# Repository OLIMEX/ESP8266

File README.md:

README
======

These apps accomplish the following:

-- ESP8266-EVB-blinkLED : Blink by green LED on ESP8266-EVB

-- arduino_style :

-- esphttpd : Advanced web-server for ESP8266-EVB (Config, Rele, Button).

## Build toolchain

https://github.com/pfalcon/esp-open-sdk is easy to use, it basically does all on its own.

- Clone the repository to ```/opt/Espressif``` (or somewhere else, this path seems to be preferred by some people)
- Install dependencies: ```sudo apt-get install make unrar-free autoconf automake libtool gcc g++ gperf flex bison texinfo gawk ncurses-dev libexpat-dev python sed help2man```
- ```make```, not as root - wait a few minutes, done.
- Add ```export PATH="${PATH}:/opt/Espressif/xtensa-lx106-elf/bin"``` to your .bashrc, .profile, .zshrc, whatever. Or just run it every time you want to use the toolchain.

In some versions of the SDK there seems to be a problem with some type definitions. If you have problems compiling with errors that some types are not defined try opening ```xtensa-lx106-elf/xtensa-lx106-elf/sysroot/usr/include/c_types.h``` and replace ```#if 0``` near the top with ```#if 1```.

## Get esptool

Some projects use ```esptool```, which is something completely different as ```esptool.py``` and which is not installed by ```esp-open-sdk```. You can get ```esptool``` here: 
* https://github.com/tommie/esptool-ck 

or here: 
* https://github.com/themadinventor/esptool

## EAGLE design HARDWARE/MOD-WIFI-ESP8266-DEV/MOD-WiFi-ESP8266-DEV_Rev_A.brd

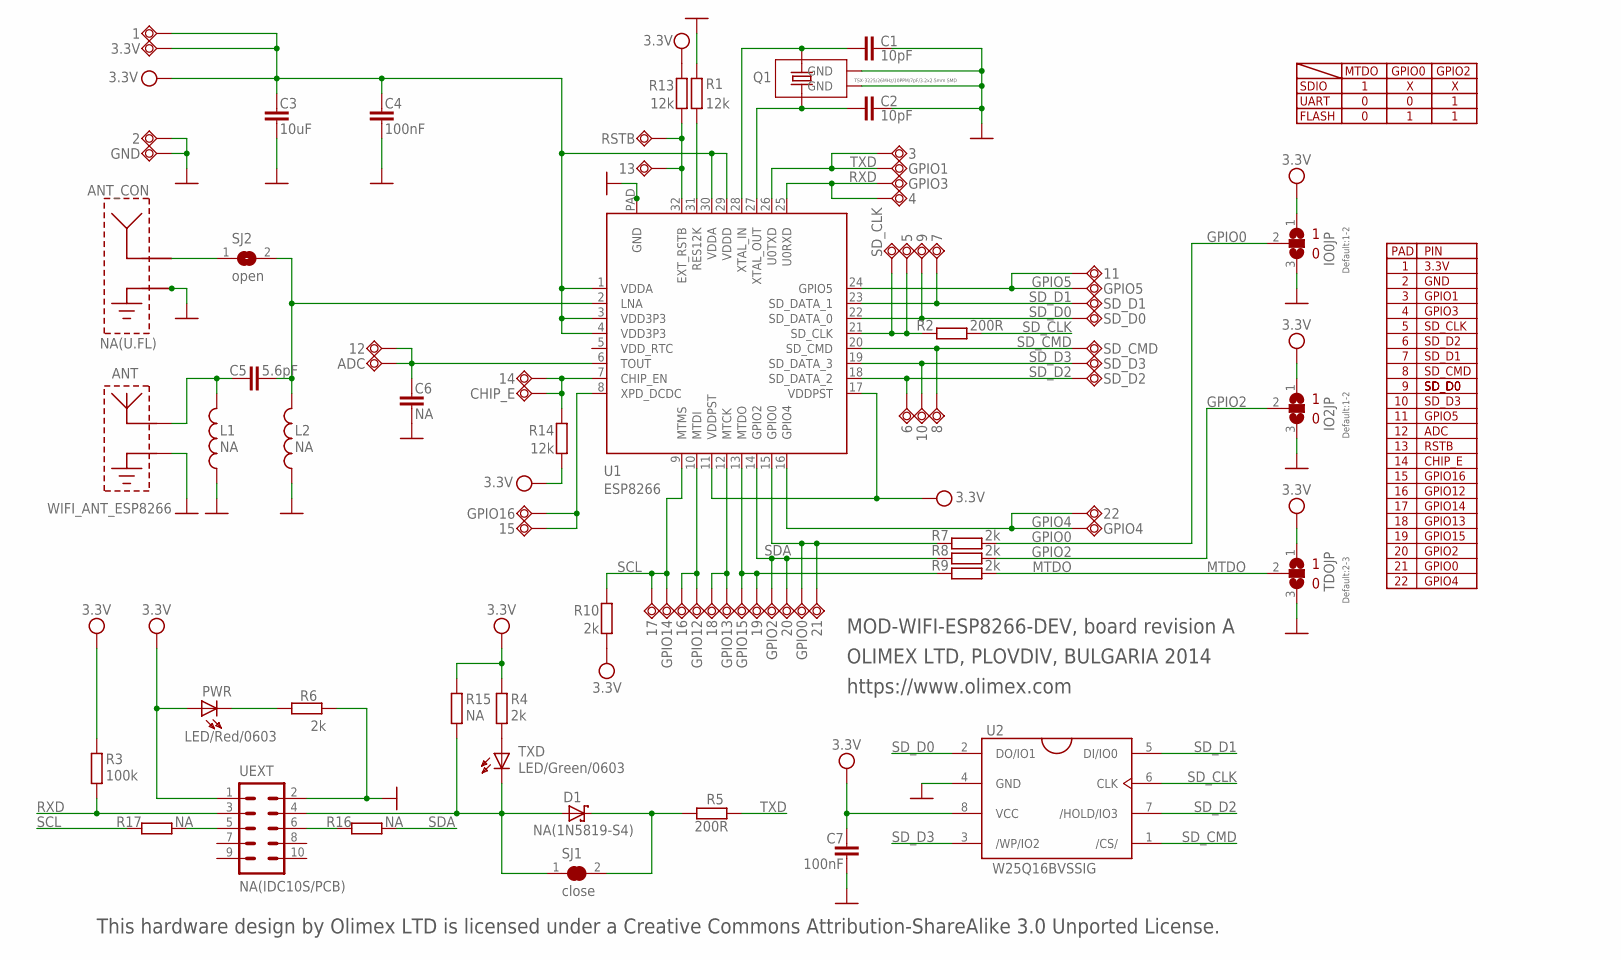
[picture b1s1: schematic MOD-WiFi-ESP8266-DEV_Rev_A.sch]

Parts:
1, 2, 3, 4, 5, 6, 7, 8, 9, 10, 11, 12, 13, 14, 15, 16, 17, 18, 19, 20, 21, 22: TESTPAD8; TESTPAD50/80
3.3V: TESTPAD40/66
ADC: TESTPAD40/66
ANT: WIFI_ANT_ESP8266; ESP8266_ANT
ANT_CON: NA(U.FL); RF_CONNECTOR_I-PEX
C1, C2: 10pF; C0402_TI
C3: 10uF; C0603_DWS
C4, C7: 100nF; C0402_TI
C5: 5.6pF; C0402_TI
C6: NA; C0402_TI
CHIP_E: TESTPAD40/66
D1: NA(1N5819-S4); SOD-123
GND: TESTPAD40/66
GPIO0, GPIO1, GPIO2, GPIO3, GPIO4, GPIO5, GPIO12, GPIO13, GPIO14, GPIO15, GPIO16: TESTPAD40/66
IO0JP, IO2JP: Default:1-2; SJ_2_SMALLER
L1, L2: NA; L0402_TI
PWR: LED/Red/0603; LED_0603
Q1: TSX-3225/26MHz/10PPM/7pF/3.2x2.5mm SMD; NX3225SA
R1, R13, R14: 12k; R0402_TI
R2, R5: 200R; R0402_TI
R3: 100k; R0402_TI
R4, R6, R7, R8, R9, R10: 2k; R0402_TI
R15, R16, R17: NA; R0402_TI
RSTB: TESTPAD40/66
SD_CLK: TESTPAD40/66
SD_CMD: TESTPAD40/66
SD_D0, SD_D1, SD_D2, SD_D3: TESTPAD40/66
SJ1: close; SJ_1_SMALLER_CLOSE_10MILS
SJ2: open; SJ_1_SMALLER
TDOJP: Default:2-3; SJ_2_SMALLER
TXD: LED/Green/0603; LED_0603
U1: ESP8266; QFN32_PAD
U2: W25Q16BVSSIG; SO8_ATMEL_FLASH
UEXT: NA(IDC10S/PCB); ML10L_PADS_FEMAIL

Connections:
GND: 2.P$1, ANT.GND, ANT_CON.1 (GND_1), ANT_CON.2 (GND_2), C1.1, C2.1, C3.2, C4.2, C6.2, C7.2, GND.P$1, IO0JP.3, IO2JP.3, L1.1, L2.1, Q1.NC_1 (GND), Q1.NC_2 (GND), R1.2, R6.1, TDOJP.3, U1.P$1 (GND), U1.P$2 (GND), U1.P$3 (GND), U1.P$4 (GND), U1.P$5 (GND), U1.P$6 (GND), U1.P$7 (GND), U1.P$8 (GND), U1.P$9 (GND), U1.PAD (GND), U2.4 (GND), UEXT.2
GPIO0: IO0JP.2, R7.1
GPIO2: IO2JP.2, R8.1
GPIO4: 22.P$1, GPIO4.P$1, U1.16 (GPIO4)
GPIO5: 11.P$1, GPIO5.P$1, U1.24 (GPIO5)
MTDO: R9.1, TDOJP.2
unnamed: D1.A, R15.1, SJ1.1, TXD.C, UEXT.4
unnamed: R4.1, TXD.A
unnamed: PWR.C, R6.2
unnamed: 21.P$1, GPIO0.P$1, R7.2, U1.15 (GPIO0)
unnamed: ANT_CON.ANT, SJ2.1
unnamed: 19.P$1, GPIO15.P$1, R9.2, U1.13 (MTDO)
unnamed: 15.P$1, GPIO16.P$1, U1.8 (XPD_DCDC)
unnamed: 16.P$1, GPIO12.P$1, U1.10 (MTDI)
unnamed: 18.P$1, GPIO13.P$1, U1.12 (MTCK)
unnamed: 14.P$1, CHIP_E.P$1, R14.1, U1.7 (CHIP_EN)
unnamed: C5.2, L2.2, SJ2.2, U1.2 (LNA)
unnamed: 13.P$1, R13.2, RSTB.P$1, U1.32 (EXT_RSTB)
unnamed: ANT.ANT, C5.1, L1.2
unnamed: D1.C, R5.2, SJ1.2
unnamed: R17.2, UEXT.5
unnamed: R16.1, UEXT.6
unnamed: 12.P$1, ADC.P$1, C6.1, U1.6 (TOUT)
unnamed: C2.2, Q1.2, U1.27 (XTAL_OUT)
unnamed: R1.1, U1.31 (RES12K)
unnamed: C1.2, Q1.1, U1.28 (XTAL_IN)
unnamed: 5.P$1, R2.2, SD_CLK.P$1, U1.21 (SD_CLK)
RXD: 4.P$1, GPIO3.P$1, R3.1, U1.25 (U0RXD), UEXT.3
SCL: 17.P$1, GPIO14.P$1, R10.1, R17.1, U1.9 (MTMS)
SDA: 20.P$1, GPIO2.P$1, R8.2, R16.2, U1.14 (GPIO2)
SD_CLK: R2.1, U2.6 (CLK)
SD_CMD: 8.P$1, SD_CMD.P$1, U1.20 (SD_CMD), U2.1 (/CS/)
SD_D0: 9.P$1, SD_D0.P$1, U1.22 (SD_DATA_0), U2.2 (DO/IO1)
SD_D1: 7.P$1, SD_D1.P$1, U1.23 (SD_DATA_1), U2.5 (DI/IO0)
SD_D2: 6.P$1, SD_D2.P$1, U1.18 (SD_DATA_2), U2.7 (/HOLD/IO3)
SD_D3: 10.P$1, SD_D3.P$1, U1.19 (SD_DATA_3), U2.3 (/WP/IO2)
TXD: 3.P$1, GPIO1.P$1, R5.1, U1.26 (U0TXD)
VCC: 1.P$1, 3.3V.P$1, C3.1, C4.1, C7.1, IO0JP.1, IO2JP.1, PWR.A, R3.2, R4.2, R10.2, R13.1, R14.2, R15.2, TDOJP.1, U1.1 (VDDA), U1.3 (VDD3P3), U1.4 (VDD3P3), U1.11 (VDDPST), U1.17 (VDDPST), U1.29 (VDDD), U1.30 (VDDA), U2.8 (VCC), UEXT.1

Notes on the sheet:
SDIO
UART
FLASH
MTDO
GPIO0
GPIO2
PAD
GPIO1
GPIO3
SD_CLK
SD_D0
SD_D1
SD_D2
SD_D3
SD_CMD
3.3V
GND
GPIO5
GPIO4
GPIO15
GPIO13
GPIO12
GPIO14
GPIO16
ADC
PIN
RSTB
CHIP_E
MOD-WIFI-ESP8266-DEV, board revision A
OLIMEX LTD, PLOVDIV, BULGARIA 2014
This hardware design by Olimex LTD is licensed under a Creative Commons Attribution-ShareAlike 3.0 Unported License.
https://www.olimex.com

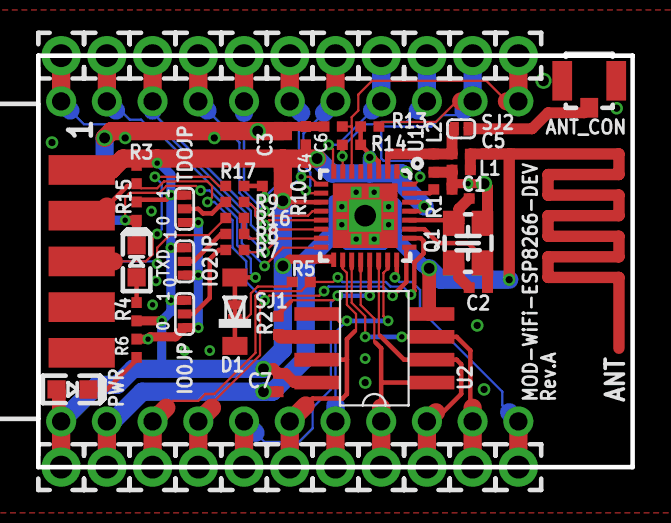
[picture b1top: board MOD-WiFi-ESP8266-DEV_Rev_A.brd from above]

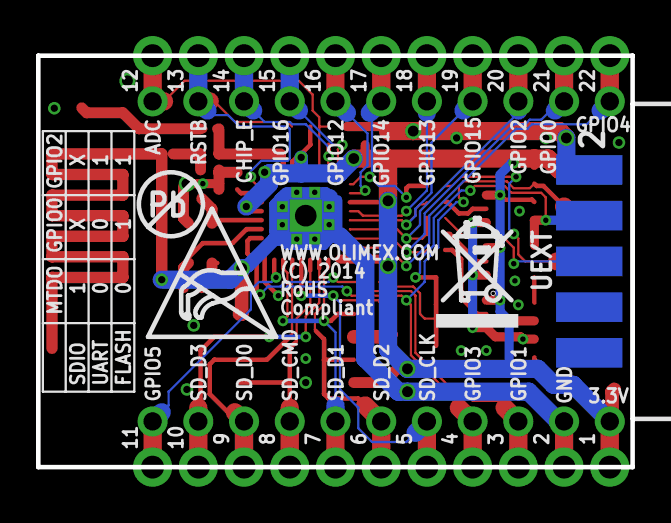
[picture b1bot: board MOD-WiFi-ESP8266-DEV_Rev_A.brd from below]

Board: 2 copper layers, 33.0 x 22.9 mm, 85 parts (4 on the bottom side), 38 nets.

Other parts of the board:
U$4: ESD_SYMBOL
U$6: PB_SMALL
U$7: RECYCLE_BIN1/8

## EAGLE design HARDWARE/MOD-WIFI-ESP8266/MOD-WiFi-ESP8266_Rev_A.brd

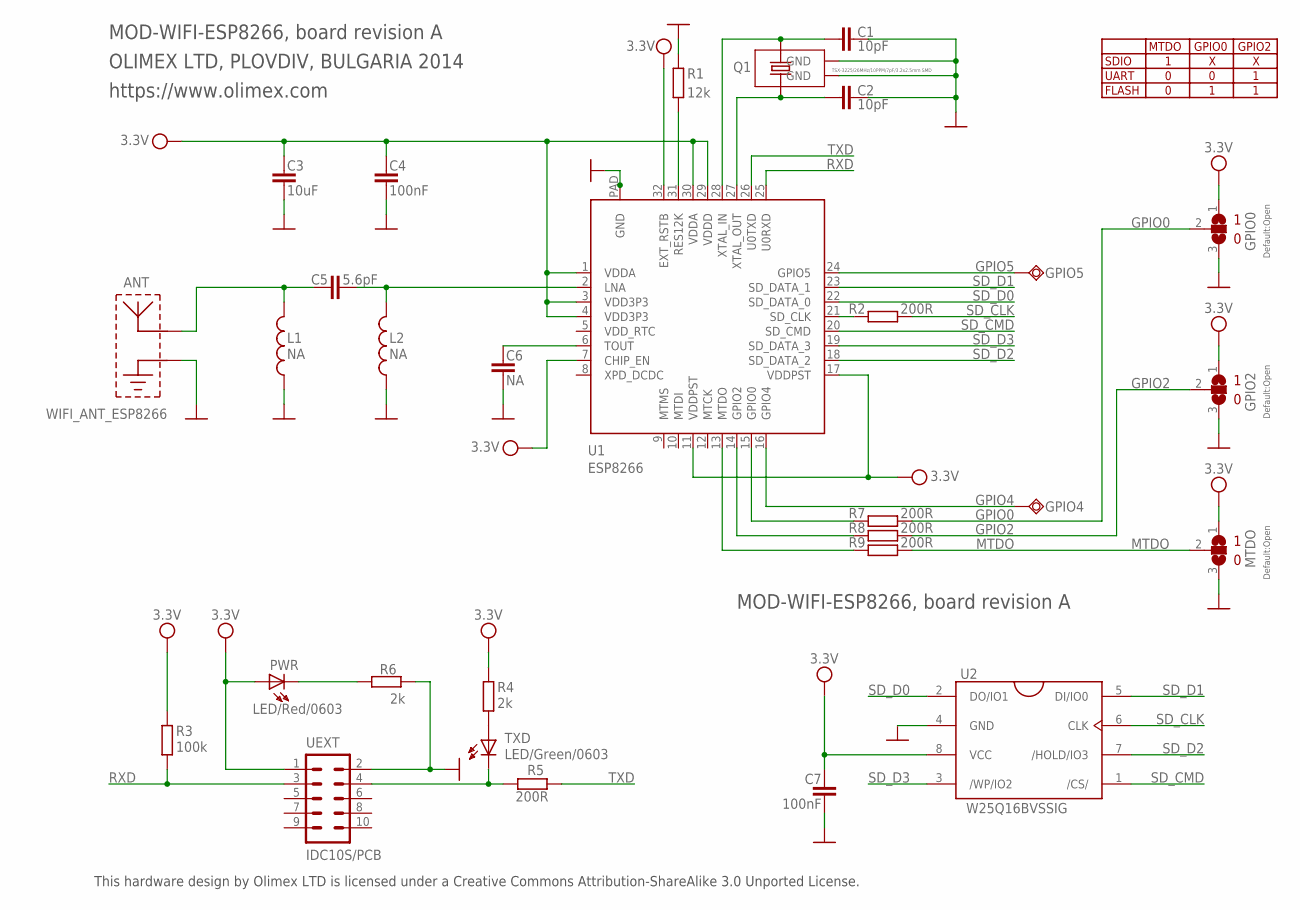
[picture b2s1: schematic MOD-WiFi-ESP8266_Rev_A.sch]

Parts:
ANT: WIFI_ANT_ESP8266; ESP8266_ANT
C1, C2: 10pF; C0402_TI
C3: 10uF; C0603_DWS
C4, C7: 100nF; C0402_TI
C5: 5.6pF; C0402_TI
C6: NA; C0402_TI
GPIO0, GPIO2: Default:Open; SJ_2_SMALLER
GPIO4, GPIO5: TESTPAD32/56
L1, L2: NA; L0402_TI
MTDO: Default:Open; SJ_2_SMALLER
PWR: LED/Red/0603; LED-0603
Q1: TSX-3225/26MHz/10PPM/7pF/3.2x2.5mm SMD; NX3225SA
R1: 12k; R0402_TI
R2, R5, R7, R8, R9: 200R; R0402_TI
R3: 100k; R0402_TI
R4, R6: 2k; R0402_TI
TXD: LED/Green/0603; LED-0603_L
U1: ESP8266; QFN32_PAD
U2: W25Q16BVSSIG; SO8_ATMEL_FLASH
UEXT: IDC10S/PCB; ML10L_PADS_FEMAIL

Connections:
GND: ANT.GND, C1.1, C2.1, C3.2, C4.2, C6.2, C7.2, GPIO0.3, GPIO2.3, L1.1, L2.1, MTDO.3, Q1.NC_1 (GND), Q1.NC_2 (GND), R1.2, R6.1, U1.P$1 (GND), U1.P$2 (GND), U1.P$3 (GND), U1.P$4 (GND), U1.P$5 (GND), U1.P$6 (GND), U1.P$7 (GND), U1.P$8 (GND), U1.P$9 (GND), U1.PAD (GND), U2.4 (GND), UEXT.2
GPIO0: GPIO0.2, R7.1
GPIO2: GPIO2.2, R8.1
GPIO4: GPIO4.P$1, U1.16 (GPIO4)
GPIO5: GPIO5.P$1, U1.24 (GPIO5)
MTDO: MTDO.2, R9.1
unnamed: R5.2, TXD.C, UEXT.4
unnamed: R4.1, TXD.A
unnamed: PWR.C, R6.2
unnamed: R7.2, U1.15 (GPIO0)
unnamed: R8.2, U1.14 (GPIO2)
unnamed: R9.2, U1.13 (MTDO)
unnamed: C5.2, L2.2, U1.2 (LNA)
unnamed: ANT.ANT, C5.1, L1.2
unnamed: C6.1, U1.6 (TOUT)
unnamed: C2.2, Q1.2, U1.27 (XTAL_OUT)
unnamed: R1.1, U1.31 (RES12K)
unnamed: C1.2, Q1.1, U1.28 (XTAL_IN)
unnamed: R2.2, U1.21 (SD_CLK)
RXD: R3.1, U1.25 (U0RXD), UEXT.3
SD_CLK: R2.1, U2.6 (CLK)
SD_CMD: U1.20 (SD_CMD), U2.1 (/CS/)
SD_D0: U1.22 (SD_DATA_0), U2.2 (DO/IO1)
SD_D1: U1.23 (SD_DATA_1), U2.5 (DI/IO0)
SD_D2: U1.18 (SD_DATA_2), U2.7 (/HOLD/IO3)
SD_D3: U1.19 (SD_DATA_3), U2.3 (/WP/IO2)
TXD: R5.1, U1.26 (U0TXD)
VCC: C3.1, C4.1, C7.1, GPIO0.1, GPIO2.1, MTDO.1, PWR.A, R3.2, R4.2, U1.1 (VDDA), U1.3 (VDD3P3), U1.4 (VDD3P3), U1.7 (CHIP_EN), U1.11 (VDDPST), U1.17 (VDDPST), U1.29 (VDDD), U1.30 (VDDA), U1.32 (EXT_RSTB), U2.8 (VCC), UEXT.1

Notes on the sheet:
SDIO
UART
FLASH
MTDO
GPIO0
GPIO2
MOD-WIFI-ESP8266, board revision A
OLIMEX LTD, PLOVDIV, BULGARIA 2014
https://www.olimex.com
This hardware design by Olimex LTD is licensed under a Creative Commons Attribution-ShareAlike 3.0 Unported License.

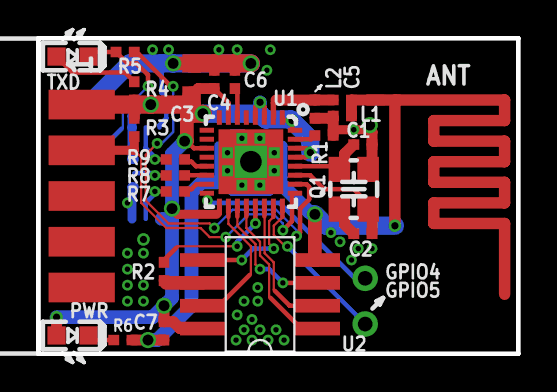
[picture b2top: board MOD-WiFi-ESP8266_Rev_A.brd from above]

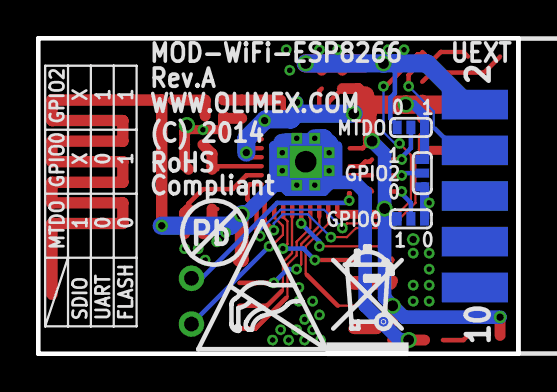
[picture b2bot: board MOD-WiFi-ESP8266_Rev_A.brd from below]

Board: 2 copper layers, 26.7 x 17.5 mm, 33 parts (7 on the bottom side), 28 nets.

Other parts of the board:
U$4: ESD_SYMBOL
U$6: PB_SMALL
U$7: RECYCLE_BIN1/8

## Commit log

2015-01-29 init
2015-01-29 ESP8266-EVB Blink TX LED Hello World code
2015-01-29 Web Server Demo for ESP8266-EVB
2015-01-29 readme description corrected
2015-01-29 fix readme
2015-01-30 Added fix for missing deps for the esphttpd server
2015-03-05 Initial commit for arduino_style
2015-03-05 Reworked README.md
2015-03-05 Add generated webpage
2015-03-16 Added Serial.read and Serial.available functions.
2015-03-17 Fixed typos in the readme and added documentation for Serial.read and Serial.available.
2015-03-17 Serial.read is compatible with Arduino's Serial.read function. Added triggers and initialization for the RxD. Changed the interrupt handler to reside in RAM and to be local.
2015-03-17 Added missing disabling and enabling of UART interrupts.
2015-03-19 Got rid of the ICACHE_RAM_ATTR. The ICACHE_RAM_ATTR in most of the cases was causing device resets. The code is tested and proven to work on ESP8266-EVB with esp-open-sdk.
2015-03-20 Add GET request support for relay.html
2015-04-26 pinout: initial version
    This is an unfinished version of a helpful pinout diagram for the
    MOD-WIFI-ESP8266-DEV module. It still needs some work to look pretty
    but may be useful even in this form.
    This was created by exporting the Eagle board design as DXF. The
    DXF file was cleaned-up using QCad, the rest was done by Inkscape.
    Once ready, PNG and PDF versions should be made available too.
2015-04-26 pinout: add legent, connect lines
2015-04-26 pinout: add pads, center on page
2015-04-26 pinout: minor details
2015-04-26 pinout: colors
2015-04-28 pinout: maybe works better
2015-05-15 remove meaningless symbols, add SPI
2015-05-22 take care about submodules
    heatshrink was missing after just clone
2015-06-01 Added useful information to README.md
2015-06-26 Olimex IoT firmware
    JSON Based Web Server and Client
2015-06-26 Update README.md
    Fix formatting
2015-06-26 Update README.md
    Fix formating
2015-06-26 Added QuickStart JavaSript Example
2015-06-26 Added QuickStart Javascript Example code
2015-06-26 Sample Application screenshot
2015-06-26 Added Sample Application screenshot
2015-06-26 Added TOC in readme.md
2015-06-26 Added TOC in readme
2015-06-26 Added command for initial firmware upload
2015-06-29 Added some example JavaScript Code
2015-06-29 Added HTML5 mobile application capabilities
2015-06-29 FIX: Default ESP8266-EVB address
2015-06-30 CAD files update
2015-06-30 Added compiling instructions
2015-07-01 Optional SSL compilation (SSL disabled by default)
2015-07-01 Description - how to enable SSL
2015-07-07 MOD-FINGER Support
2015-07-07 SDK 1.2.0 Update
2015-07-07 SDK 1.2.0 Update
    Compile notes and flash for the first time changes
2015-07-08 SDK 1.2.0 - Espressif patch
2015-07-08 Improved devices scan
2015-07-08 Connections debug improvenemt
2015-07-08 Binaries update
2015-07-09 IoT Firmawe Usage Demo
    Tweets on MOD-LED8x8RGB
2015-07-09 README Update
2015-07-09 package.json update
2015-07-10 Added license information in package.json
2015-07-10 Added License file
2015-07-10 More clear README explanation
2015-07-13 Miscellaneous fixes and Espressif SDK patches
2015-07-13 Add Example of implementation mqtt
2015-07-13 Add Example of relay control with mqtt
2015-07-14 Moved example to Arduino IDE folder
2015-07-15 Managing user timers with handle instead of pointer
2015-07-15 user timers handle - integer overflow
2015-07-16 Add README file with installation and usage instruction
2015-07-17 MOD-EMTR Support
2015-07-22 MOD-EMTR cconfiguration
2015-07-23 Devices down functionality
2015-08-18 SDK 1.3.0
2015-09-04 FIX: SDK Sample Application cache manifest
2015-09-07 FIX: I2C Delay
2015-09-11 FIX: WebSocket rapid message sending
2015-09-11 Sample application - module tabs improvement
2015-09-11 FIX: Deprecated SDK call
2015-09-15 WebClient - debug message fix
2015-09-15 Sample Application - Station Config disable IP configuration when DHCP is enabled
2015-09-25 SDK 1.4.0
2015-09-25 WiFi events handling
2015-09-25 Relay auto switch off after specified delay
2015-09-25 Relay auto switch off - description
2015-09-30 Key driver improvements
2015-09-30 ESP8266-EVB-BAT Support
2015-10-01 Conditional modules compiling
2015-10-12 WebClient debug message fix
2015-10-12 FIX: Battery ADC filter
2015-10-12 FIX: SSL max packet len
2015-10-12 FIX: MOD-FINGER timeouts
2015-10-12 FIX: WebClient SSL request
2015-10-12 FIX: Font % sign
2015-11-01 remove readme file
2015-11-01 Add Example with relay,switch state on button press
2015-11-01 Add README file , edit package.json
2015-11-06 SDK 1.4.0 - SSL set default key and certificate
2015-11-06 UART0 swap and UART1 enable in user config
2015-11-06 FIX: User config according to SDK 1.4.0
2015-11-06 FEATURE: UTF8 Support
2015-11-06 FIX: Battery event filter and Flash regions size
2015-11-06 SDK 1.4.1 pre2
2015-11-06 SDK 1.4.1 pre3
2015-11-06 FEATURE: ESP-SWITCH2 Support
2015-11-06 Sample Application Refactory
2015-11-06 SDK 1.4.1 pre5
2015-11-06 FEATURE: ESP-BADGE Support
2015-11-06 IoT Demo - v 2.0.0
2015-11-06 IoT Demo - v 2.0.1
2015-11-06 Removing some old unused files
2015-11-07 Add example of using esp8266-iotjs package
2015-11-07 Add Simple demo of using esp8266-iotjs npm package
2015-11-07 remove wrogn uploaded Files
2015-11-07 add dependence in package.json
2015-11-07 Fix Text in ReadMe
2015-11-09 Some MessageQueue fixes
2015-11-10 Optional WiFi Debug compiling and SWITCH2 switch events refactoring
2015-11-11 Minor connection initialization fixes
2015-11-17 HTML Application Update
2015-11-26 Make file fix
2015-12-03 fix whitespace errors in gen_appbin.py
    This was done using a script from the Python distribution:
    /usr/lib/python3.5/Tools/scripts/reindent.py tools/gen_appbin.py
2015-12-03 allow overriding the python binary used for gen_appbin.py
2015-12-16 grammar, baby!
2015-12-22 SDK 1.5.0, SWITCH1, SWITCH2, DIMMER, PLUG, MOD_EMTR
2016-01-17 WEBCLIENT fixes: - request cleanup - timer cleanup when cleaning request - receiving chunked responses HTTP1.1 (eg. thingspeak.com does) - timeout timer moved to the beginning of request-response han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
2016-01-21 FIX: WebSocket frame segmentation at TCP level
2016-01-25 SDK 1.5.1
2016-01-25 Initial firmware load command update
    - new boot-loader
    - clear firmware config parameters
2016-01-25 FIX: Broken HTML Application REST mode
2016-01-26 Dispaly Reset Info in General Config Tab
2016-01-27 Force 802.11g mode
2016-01-27 Dispaly PHY Mode in General Config Tab
2016-01-27 FIX: Event messages memory alloaction
2016-01-28 Set WiFi station hostname
2016-01-29 Display WiFi channel in General Config Tab
2016-01-29 Keep SWITCH1 relay state after soft reset
2016-02-04 Keep SWITCH2 relay state after soft reset, enable button and EMTR
2016-02-12 FIX: WebClient - condition order
2016-02-15 SDK 1.5.2
2016-02-24 Hostname config added
2016-02-24 Hostname string size fix
2016-02-25 FIX: Hostname size & application cache manifest version
2016-02-25 SWITCH2 event message for modified state only
2016-03-01 FIX: WebClient - reconnect to IoT server issues
2016-03-07 FIX: WebClient - retry after 10 sec
2016-03-07 FIX: SWITCH1 and SWITCH2 reading filter and events raising
2016-03-09 Updated ESP8266 hardware files
2016-03-14 REFACTORY: All relays to support SET, TOGGLE and ON_OFF commands
2016-03-14 Add name for registered devices
2016-03-15 FIX: WebClient - Finishing chunked message. Closes #40
2016-03-16 SDK 1.5.2 - SSL patch
2016-03-16 FIX: WebClient - MEMORY LEAK along with some refactoring
2016-03-24 FIX: WebServer - connection should not be deleted. Closes #41
2016-04-12 FIX: WebSocket - upgrade connection memory leak, WebServer - Free message queue on disconnect , MOD-EMTR - events on change,
2016-04-18 SDK 1.5.3
2016-04-19 FIX: Delay button Long press restore defaults action
2016-05-05 FIX: Functions in RAM by oversight
2016-05-05 FIX: Delay button "Long press" restore defaults
2016-05-16 WebSocket messages REF support
2016-05-27 SDK 1.5.4
2016-05-27 FIX: MOD-TC-MK2 and BATTERY input filtering
2016-05-27 FIX: MOD-TC-MK2 and BATTERY input filtering refining
2016-06-01 FIX: WebSocket - client SSL send
2016-06-01 FIX: More input filtering
2016-06-01 HTML Application minor fixes
2016-07-18 Some new features and fixes to get IoT Server ready
    FEATURES:
    Firmware version and build (build shell script)
    Device preferences stored into flash
    Report reset reason on first IoT server connect
    Restart and Reset to defaults commands
    I2C Clock Stretching
2016-07-20 SDK Patch 1.5.4.1
2016-07-26 FIX: EMTR counters formating
2016-07-26 FIX: EMTR relay toggle on short release
2016-07-26 FIX: PLUG Led blink timers
2016-07-26 FIX: Delayed AP and Station configuration set to be able to send response
2016-07-26 SDK 2.0.0
2016-07-27 FIX: EMTR calibration
2016-07-27 FIX: Button driver PRESS handling
2016-09-07 SDK Patch 20160809
2016-09-07 FIX: Relay toggle raise event
2016-09-07 FIX: MOD-EMTR miscellaneous calibration and calculations
2016-09-07 WebClient custom port configuration support
2016-09-09 Create Tesr
2016-09-23 FIX: Missing SDK library files
2016-11-08 FIX: Limit WiFi scan result to 5 AP with higest signal level
2016-11-08 Prepare for split in new repository
2016-11-08 Moved
2017-05-01 change author
2017-10-09 minor changes to readme guide
    minor changes to readme guide
2018-03-08 Update
    Hardware revision B1
2018-09-11 add Licensee
2018-09-11 Update
    Updated directory structure
2018-09-11 Update
    Structure fix
2021-09-02 Update
    New revision due to new SPI memory
2026-01-07 addingn 3d printed case files

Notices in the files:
HARDWARE/MOD-WIFI-ESP8266-DEV/MOD-WiFi-ESP8266-DEV_Rev_A.brd:
(C) 2014
